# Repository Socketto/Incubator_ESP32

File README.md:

### Project Overview

This project was born out of the desire to see if supermarket quail eggs are actually fertile (unlike chicken eggs). The goal was to explore the possibility of incubating quail eggs and monitor their development.

---

### The Incubator Design

To achieve this, I designed an **incubator for birds** using a thermally insulated plastic box. The setup is simple but effective for maintaining the right conditions for incubation.

---

### Temperature and Humidity Control

I managed the **temperature** and **humidity control** using a custom-designed board that features an **ESP32-WROOM** chip. This board was programmed using the **Arduino IDE**, providing full control over the incubator's conditions.

For heating, I used a **220V heater**, which I modulated using a **trimmer**. To maintain proper humidity inside, I used an **electric room humidifier**.

---

### User Interface and Remote Control

The board is equipped with a **color TFT graphical interface**, making it easy to monitor and control the incubator. Additionally, the incubator is controlled directly via a **Telegram bot** on your phone, allowing for remote management. 

For initial setup (WiFi credentials, Telegram token, and password), I added a feature that allows the board to switch to **Access Point (AP) mode**, enabling configuration through a minimal web server. These values are saved in the non-volatile memory of the ESP32, so they persist through future restarts.

---

### Flexibility and Future Expansion

Currently, the software is configured to handle the **incubation periods**, **temperatures**, and **humidity** levels for chickens and quails. However, the system can easily be extended to accommodate other types of birds as well.

---

### Data Monitoring and Remote Supervision

The incubator's data can be communicated via **MQTT**, allowing for remote tracking of the incubation process from an external monitoring environment. I personally use **Node-RED** to monitor the data in real-time.

---

### Sharing the Experience

To make the project even more enjoyable, I set up a **live stream on Twitch** of the incubation process. This allows my friends to join in on the excitement and witness the first moments of life for the **❤️chicks❤️**.
  
[twitch channel](https://www.twitch.tv/socketto87)

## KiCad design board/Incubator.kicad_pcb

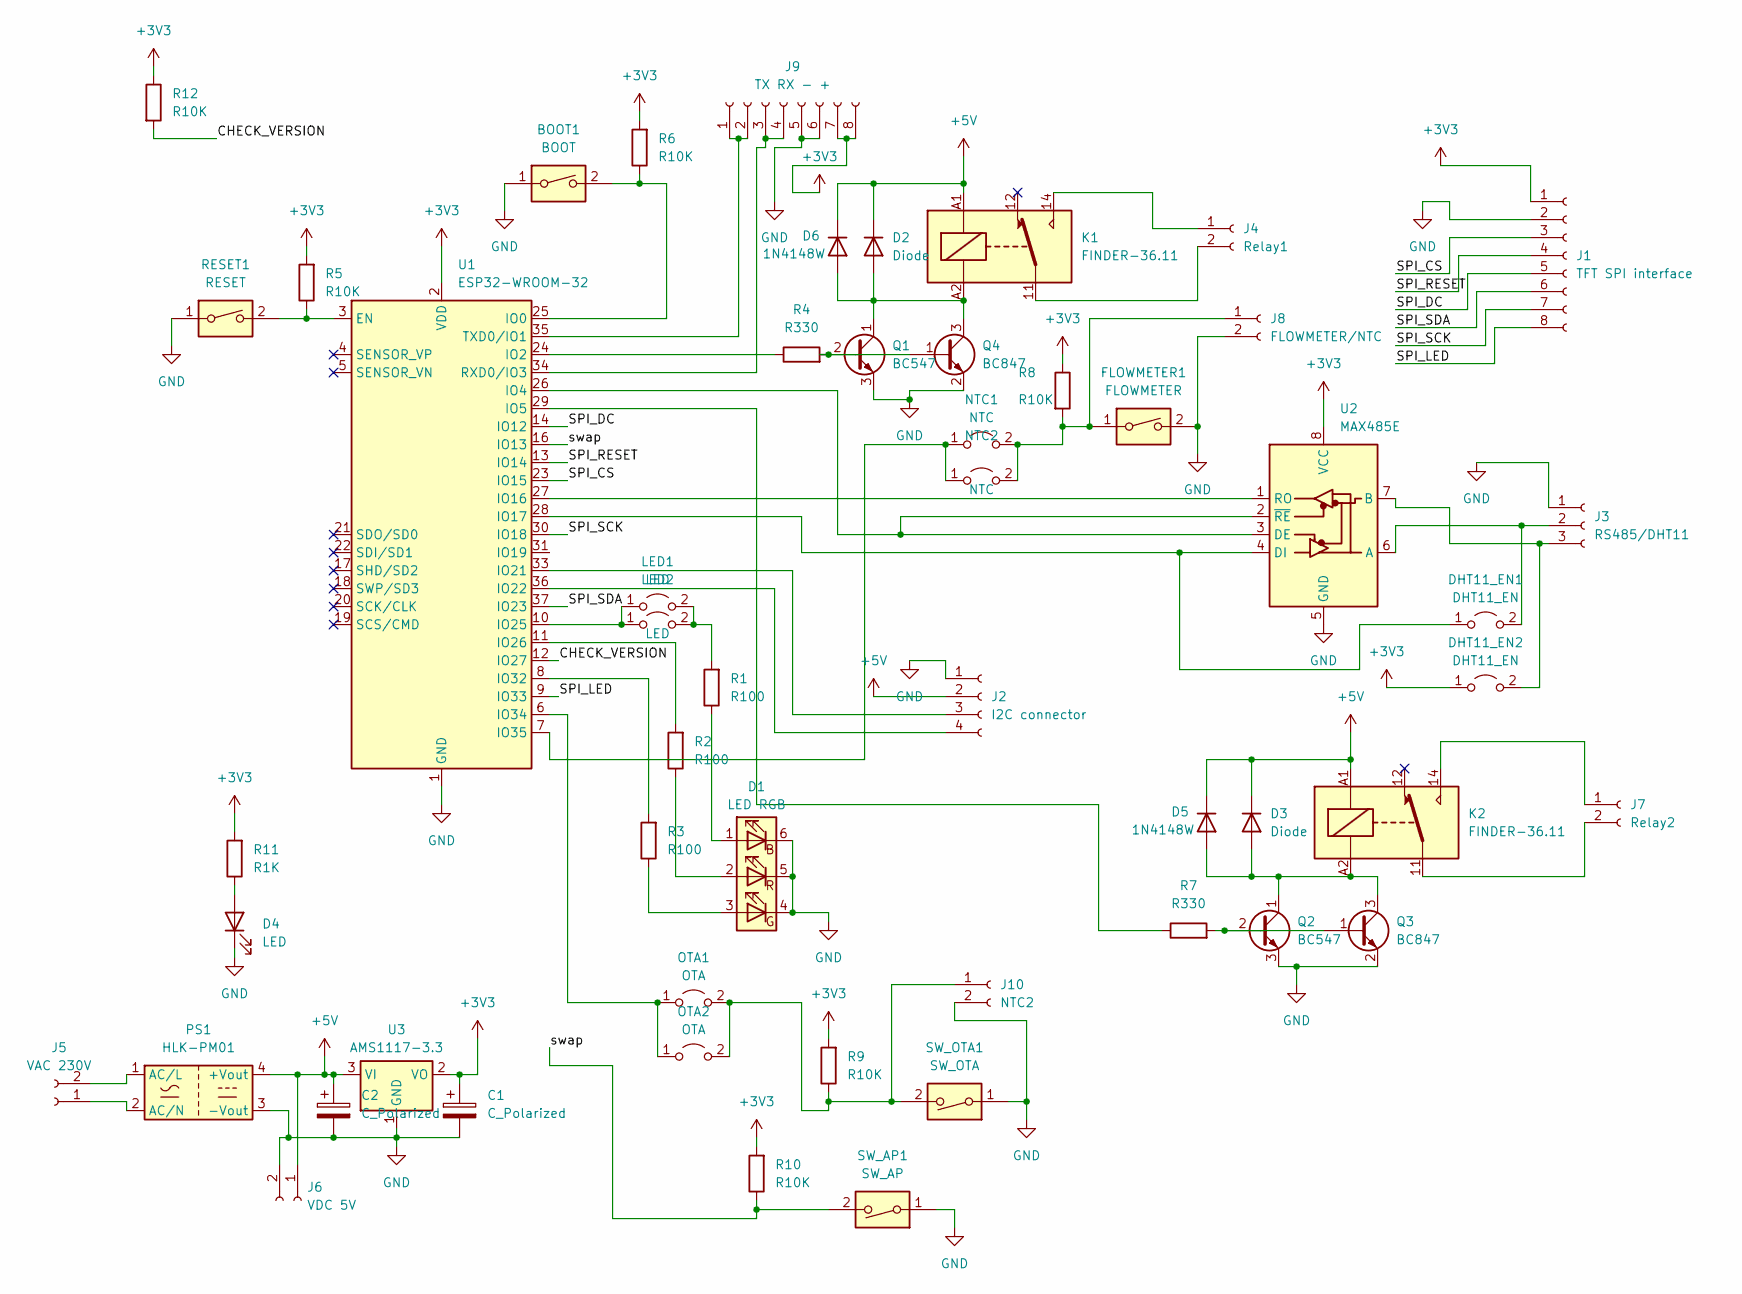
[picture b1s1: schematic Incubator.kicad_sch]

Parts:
BOOT1: BOOT; SW_PUSH_6mm_H4.3mm
C1, C2: C_Polarized; CP_Radial_D10.0mm_P5.00mm
D1: LED RGB; LED_RGB_5050-6
D2, D3: Diode; D_DO-35_SOD27_P10.16mm_Horizontal
D4: LED; LED_1206_3216Metric_Pad1.42x1.75mm_HandSolder
D5, D6: 1N4148W; D_SOD-123
DHT11_EN1, DHT11_EN2: DHT11_EN; SolderJumper-2_P1.3mm_Open_RoundedPad1.0x1.5mm
FLOWMETER1: FLOWMETER; SW_PUSH_6mm_H4.3mm
J1: TFT SPI interface; JST_XH_B8B-XH-AM_1x08_P2.50mm_Vertical
J2: I2C connector; JST_XH_B4B-XH-AM_1x04_P2.50mm_Vertical
J3: RS485/DHT11; PhoenixContact_MSTBA_2,5_3-G_1x03_P5.00mm_Horizontal
J4: Relay1; TerminalBlock_Altech_AK300-2_P5.00mm
J5: VAC 230V; TerminalBlock_Altech_AK300-2_P5.00mm
J6: VDC 5V; JST_XH_B2B-XH-A_1x02_P2.50mm_Vertical
J7: Relay2; TerminalBlock_Altech_AK300-2_P5.00mm
J8: FLOWMETER/NTC; TerminalBlock_Altech_AK300-2_P5.00mm
J9: TX RX - +; PinSocket_2x04_P2.54mm_Vertical
J10: NTC2; JST_XH_B2B-XH-A_1x02_P2.50mm_Vertical
K1, K2: FINDER-36.11; Relay_SPDT_Finder_36.11
LED1: LED; SolderJumper-2_P1.3mm_Open_RoundedPad1.0x1.5mm
LED2: LED; PinHeader_1x02_P2.54mm_Vertical
NTC1: NTC; PinHeader_1x02_P2.54mm_Vertical
NTC2: NTC; SolderJumper-2_P1.3mm_Open_RoundedPad1.0x1.5mm
OTA1: OTA; PinHeader_1x02_P2.54mm_Vertical
OTA2: OTA; SolderJumper-2_P1.3mm_Open_RoundedPad1.0x1.5mm
PS1: HLK-PM01; Converter_ACDC_HiLink_HLK-PMxx
Q1, Q2: BC547; TO-92_Inline
Q3, Q4: BC847; SOT-23
R1, R2, R3: R100; R_1206_3216Metric
R4, R7: R330; R_1206_3216Metric
R5, R6, R8, R9, R10, R12: R10K; R_1206_3216Metric
R11: R1K; R_1206_3216Metric
RESET1: RESET; SW_PUSH_6mm_H4.3mm
SW_AP1: SW_AP; SW_PUSH_6mm_H4.3mm
SW_OTA1: SW_OTA; SW_PUSH_6mm_H4.3mm
U1: ESP32-WROOM-32
U2: MAX485E; SO-8_3.9x4.9mm_P1.27mm
U3: AMS1117-3.3; SOT-223-3_TabPin2

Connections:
+3V3: C1.1, DHT11_EN2.1 (A), J1.1, J9.7, J9.8, R5.2, R6.2, R8.1, R9.2, R10.2, R11.2, R12.1, U1.2 (VDD), U2.8 (VCC), U3.2 (VO)
+5V: C2.1, D2.1 (K), D3.1 (K), D5.1 (K), D6.1 (K), J2.2, J6.1, K1.A1, K2.A1, PS1.4 (+Vout), U3.3 (VI)
/CHECK_VERSION: R12.2, U1.12 (IO27)
/SPI_CS: J1.3, U1.23 (IO15)
/SPI_DC: J1.5, U1.14 (IO12)
/SPI_LED: J1.8, U1.9 (IO33)
/SPI_RESET: J1.4, U1.13 (IO14)
/SPI_SCK: J1.7, U1.30 (IO18)
/SPI_SDA: J1.6, U1.37 (IO23)
/swap: R10.1, SW_AP1.2, U1.16 (IO13)
GND: BOOT1.1, C1.2, C2.2, D1.4 (GK), D1.5 (RK), D1.6 (BK), D4.1 (K), FLOWMETER1.2, J1.2, J2.1, J3.1, J6.2, J8.2, J9.5, J9.6, J10.2, PS1.3 (-Vout), Q1.3 (E), Q2.3 (E), Q3.2 (E), Q4.2 (E), RESET1.1, SW_AP1.1, SW_OTA1.1, U1.1 (GND), U1.15 (GND), U1.38 (GND), U1.39 (GND), U2.5 (GND), U3.1 (GND)
unnamed: D1.1 (BA), R1.1
unnamed: D1.3 (GA), R3.1
unnamed: D1.2 (RA), R2.1
unnamed: D2.2 (A), D6.2 (A), K1.A2, Q1.1 (C), Q4.3 (C)
unnamed: D3.2 (A), D5.2 (A), K2.A2, Q2.1 (C), Q3.3 (C)
unnamed: D4.2 (A), R11.1
unnamed: DHT11_EN1.1 (A), U1.28 (IO17), U2.4 (DI)
unnamed: DHT11_EN1.2 (B), J3.2, U2.6 (A)
unnamed: DHT11_EN2.2 (B), J3.3, U2.7 (B)
unnamed: J2.3, U1.33 (IO21)
unnamed: J2.4, U1.36 (IO22)
unnamed: J4.1, K1.14
unnamed: J4.2, K1.11
unnamed: J5.1, PS1.2 (AC/N)
unnamed: J5.2, PS1.1 (AC/L)
unnamed: J7.1, K2.14
unnamed: J7.2, K2.11
unnamed: FLOWMETER1.1, J8.1, NTC1.2 (B), NTC2.2 (B), R8.2
unnamed: J9.1, J9.2, U1.35 (TXD0/IO1)
unnamed: J9.3, J9.4, U1.34 (RXD0/IO3)
unnamed: J10.1, OTA1.2 (B), OTA2.2 (B), R9.1, SW_OTA1.2
unnamed: LED1.1 (A), LED2.1 (A), U1.10 (IO25)
unnamed: LED1.2 (B), LED2.2 (B), R1.2
unnamed: NTC1.1 (A), NTC2.1 (A), U1.7 (IO35)
unnamed: OTA1.1 (A), OTA2.1 (A), U1.6 (IO34)
unnamed: Q1.2 (B), Q4.1 (B), R4.2
unnamed: Q2.2 (B), Q3.1 (B), R7.2
unnamed: R5.1, RESET1.2, U1.3 (EN)
unnamed: BOOT1.2, R6.1, U1.25 (IO0)
unnamed: R4.1, U1.24 (IO2)
unnamed: U1.26 (IO4), U2.2 (~RE), U2.3 (DE)
unnamed: R7.1, U1.29 (IO5)
unnamed: U1.27 (IO16), U2.1 (RO)
unnamed: R2.2, U1.11 (IO26)
unnamed: R3.2, U1.8 (IO32)

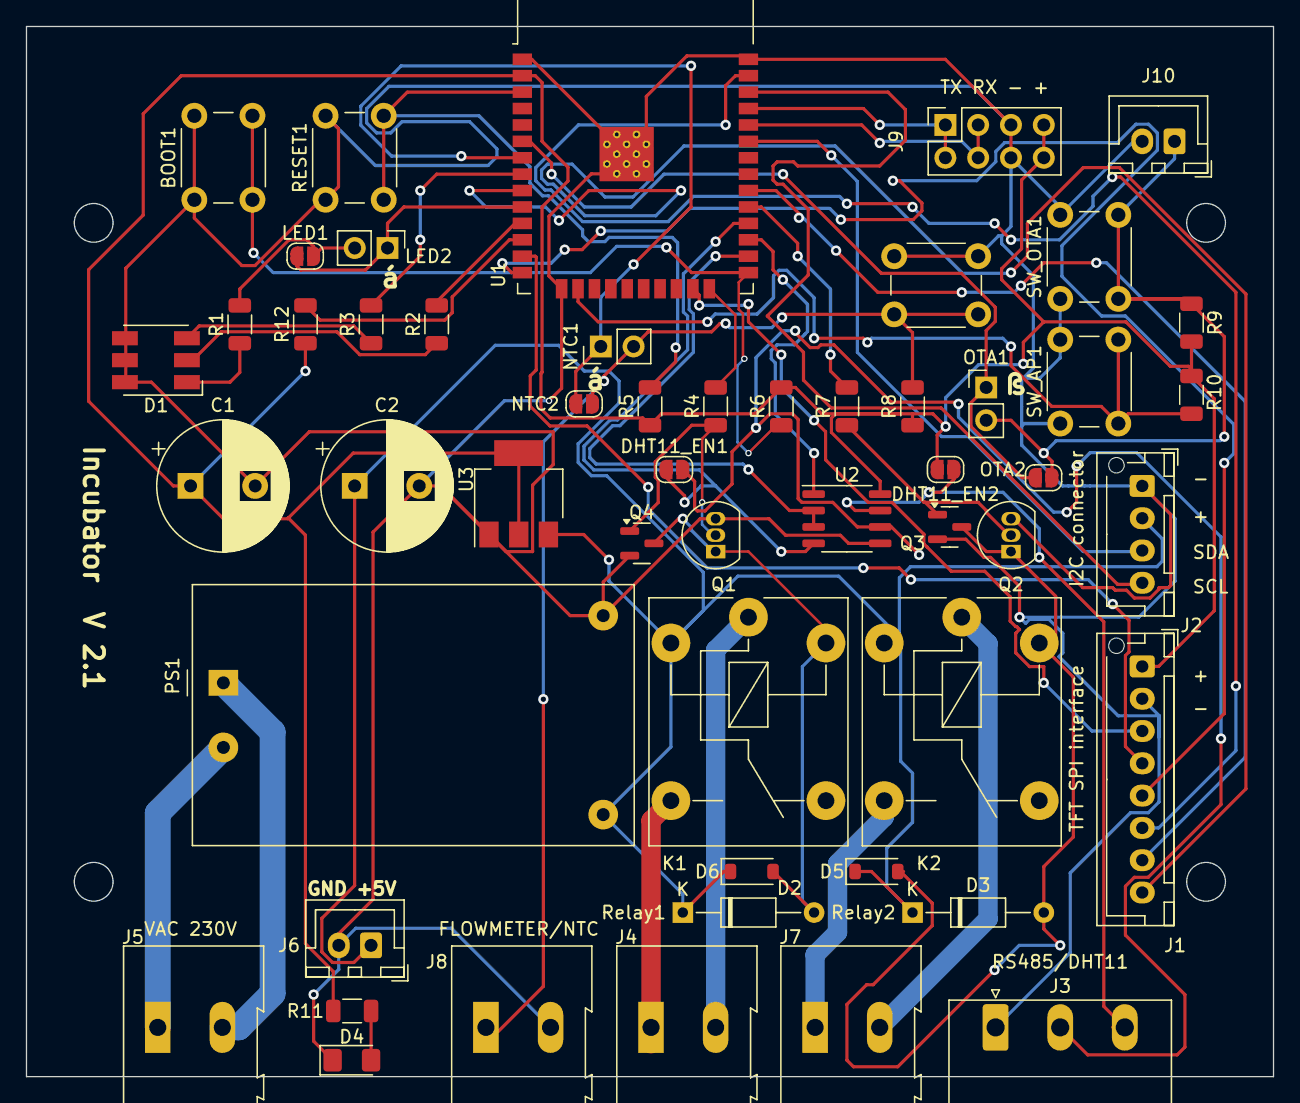
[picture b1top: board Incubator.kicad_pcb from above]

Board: 2 copper layers, 96.5 x 81.3 mm, 53 parts (0 on the bottom side), 46 nets.

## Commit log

2025-03-07 [ADD] Add first version
2025-03-24 [ADD] Add first draft to change ON OFF of heater dinamically
2025-03-25 [ENH] Enhance management of temperature
2025-03-26 [UPD] Update messages and add offset for NTC
2025-03-26 [UPD] Save value on preferences to set the incubator temperature regulation
2025-03-27 [ADD] Add command and use another Preferences for temperature modulation
2025-04-01 [FIX] Fix some issue on management of messages of Telegram and add check on preferences_command.begin("incu1") at start
2025-04-18 [UPD] Update board
2025-06-05 [UPD] Update days and avoid wire interferences
2025-07-17 [FIX] Stable version
